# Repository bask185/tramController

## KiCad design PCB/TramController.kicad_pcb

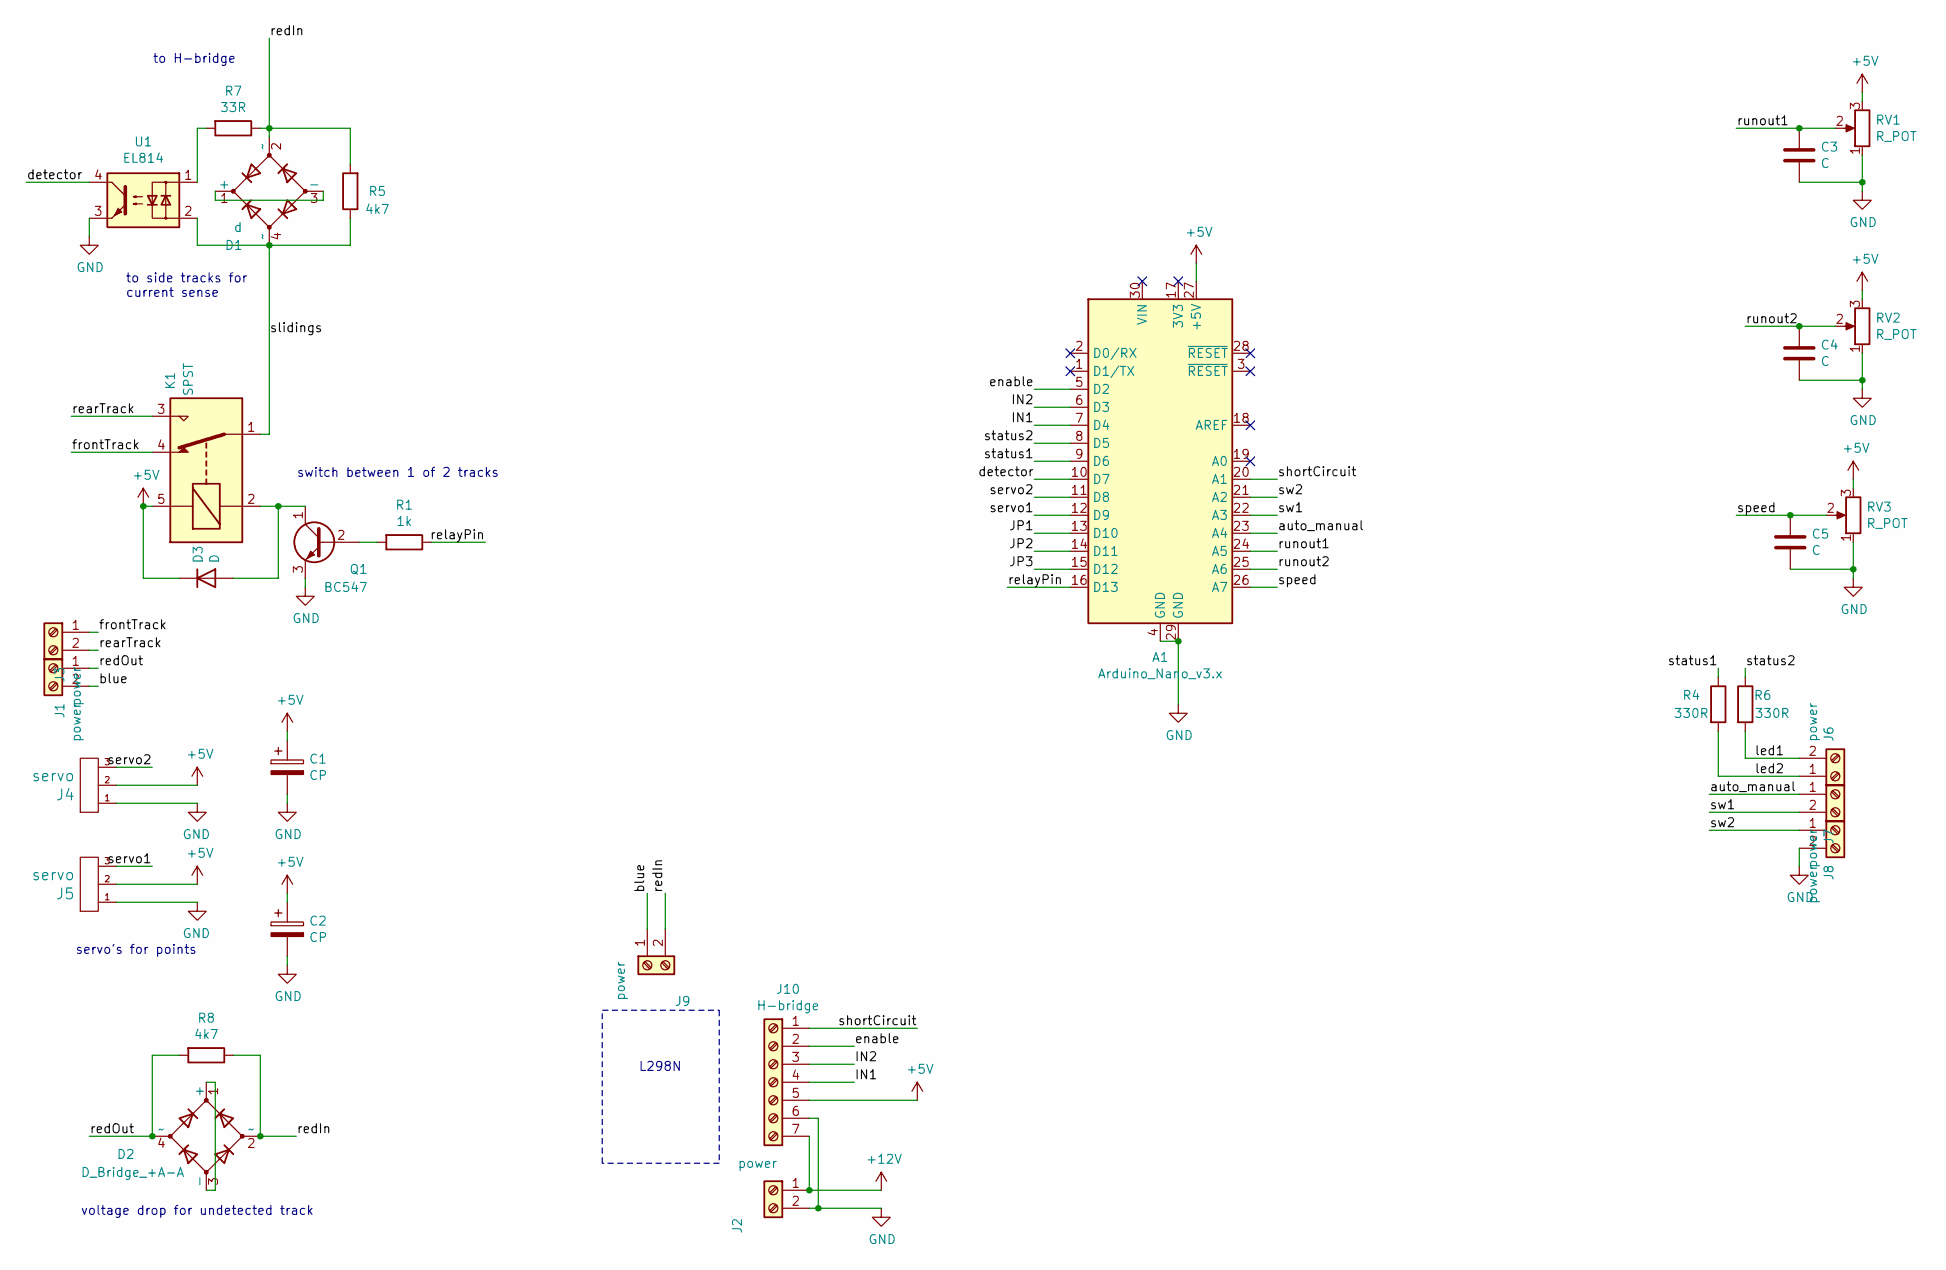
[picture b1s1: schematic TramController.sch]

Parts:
A1: Arduino_Nano_v3.x; Arduino_Nano
C1, C2: CP; CP_Radial_D4.0mm_P1.50mm
C3, C4, C5: C; C_Disc_D3.0mm_W1.6mm_P2.50mm
D1: d; Diode_Bridge_Round_D9.0mm
D2: D_Bridge_+A-A; Diode_Bridge_Round_D9.0mm
D3: D; D_A-405_P7.62mm_Horizontal
J1, J2, J3, J6, J7, J8, J9: power; TerminalBlock_Phoenix_MKDS-1,5-2-5.08_1x02_P5.08mm_Horizont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
J4, J5: servo; PinHeader_1x03_P2.54mm_Vertical
J10: H-bridge; TerminalBlock_Phoenix_MKDS-1,5-7-5.08_1x07_P5.08mm_Horizont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
K1: SPST; Relay_SPDT_SANYOU_SRD_Series_Form_C
Q1: BC547; TO-92_Inline
R1: 1k; R_Axial_DIN0204_L3.6mm_D1.6mm_P7.62mm_Horizontal
R4, R6: 330R; R_Axial_DIN0204_L3.6mm_D1.6mm_P7.62mm_Horizontal
R5, R8: 4k7; R_Axial_DIN0204_L3.6mm_D1.6mm_P7.62mm_Horizontal
R7: 33R; R_Axial_DIN0204_L3.6mm_D1.6mm_P7.62mm_Horizontal
RV1, RV2, RV3: R_POT; Potentiometer_Runtron_RM-065_Vertical
U1: EL814; DIP-4_W7.62mm

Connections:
+5V: A1.27 (+5V), C1.1, C2.1, D3.1 (K), J4.2, J5.2, J10.5, K1.5, RV1.3, RV2.3, RV3.3
+12V: J2.1, J10.7
/IN1: A1.7 (D4), J10.4
/IN2: A1.6 (D3), J10.3
/JP1: A1.13 (D10)
/JP2: A1.14 (D11)
/JP3: A1.15 (D12)
/auto_manual: A1.23 (A4), J7.1
/blue: J1.2, J9.1
/detector: A1.10 (D7), U1.4
/enable: A1.5 (D2), J10.2
/frontTrack: J3.1, K1.4
/led1: J6.2, R6.2
/led2: J6.1, R4.2
/rearTrack: J3.2, K1.3
/redIn: D1.2 (~~), D2.2 (~~), J9.2, R5.2, R7.1, R8.1
/redOut: D2.4 (~~), J1.1, R8.2
/relayPin: A1.16 (D13), R1.1
/runout1: A1.24 (A5), C3.1, RV1.2
/runout2: A1.25 (A6), C4.1, RV2.2
/servo1: A1.12 (D9), J5.3
/servo2: A1.11 (D8), J4.3
/shortCircuit: A1.20 (A1), J10.1
/slidings: D1.4 (~~), K1.1, R5.1, U1.2
/speed: A1.26 (A7), C5.1, RV3.2
/status1: A1.9 (D6), R4.1
/status2: A1.8 (D5), R6.1
/sw1: A1.22 (A3), J7.2
/sw2: A1.21 (A2), J8.1
GND: A1.4 (GND), A1.29 (GND), C1.2, C2.2, C3.2, C4.2, C5.2, J2.2, J4.1, J5.1, J8.2, J10.6, Q1.3 (E), RV1.1, RV2.1, RV3.1, U1.3
unnamed: D1.1 (+), D1.3 (-)
unnamed: D2.1 (+), D2.3 (-)
unnamed: D3.2 (A), K1.2, Q1.1 (C)
unnamed: Q1.2 (B), R1.2
unnamed: R7.2, U1.1

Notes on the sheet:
voltage drop for undetected track
switch between 1 of 2 tracks
servo's for points
to H-bridge
to side tracks for current sense
L298N

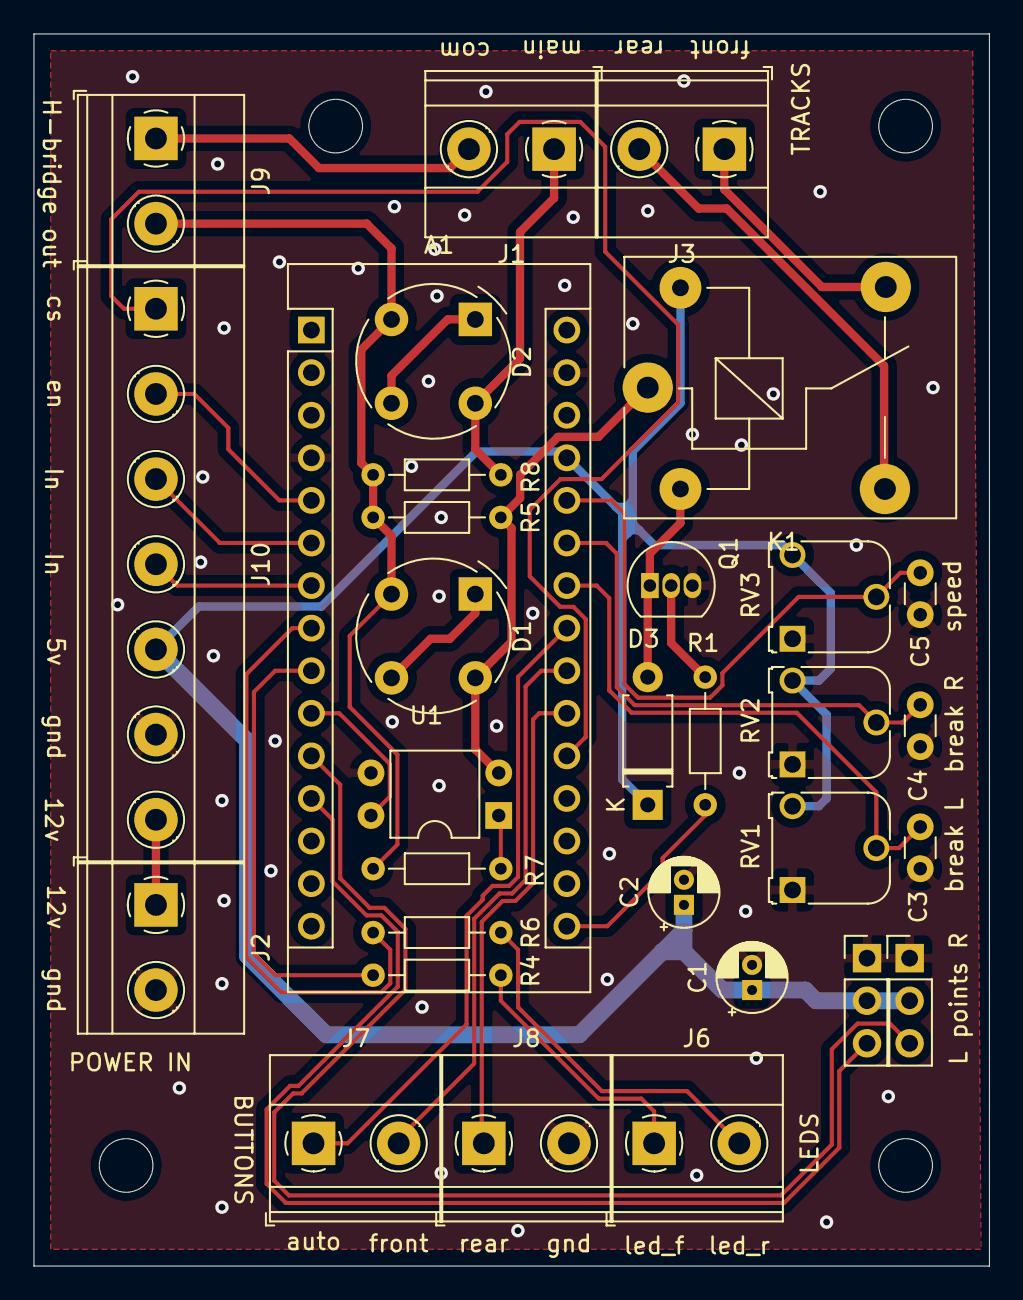
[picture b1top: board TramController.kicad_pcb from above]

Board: 2 copper layers, 57.0 x 73.5 mm, 31 parts (0 on the bottom side), 32 nets.

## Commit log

2021-08-30 added initial PCB files
2021-08-30 added 2 pdfs with schematic and pcb. pcb is a misery
2021-09-14 added all source code. Code is 100% compilable and might ferry well be finished already
2021-09-14 added serial debug texts, added 1 second delay after train left the station.
2021-09-14 flipped 2 servo positions so that they can be placed contra.
2021-09-14 replaced schematic with a more up to date one
2021-09-14 added PDF of the schematic as well as a script to help put gerbers in a folder
2021-11-18 added short circuit function and modified the weistra class, with a private power boolean
2022-01-05 discovered one minor bug. I may have forgotton to set the direction pins properly
2022-01-06 Changed debouncing method of the detector to work more reliably.
    Also added the possibility to reset the state machine by holding down both direction buttons.
    Added a 1000ms delay before measuring current when the train is departing.
    TODO:
    if a train takes too long to depart, it is still drawing current but is stuck. The power must be cut off and the state machine must be reset.
    if a train takes too long to arrive at the station Leds need to blink to indicate this.
    There also needs to be a blinking action for when there is a short circuit.
2022-01-10 code is made to work on some scrambled electronics tied on a piece of work. State machine has proven too work efficiently
2022-01-27 added pcb files.
